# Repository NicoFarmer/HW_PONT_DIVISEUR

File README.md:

# HW_PONT_DIVISEUR
Pont diviseur de tension sur petite carte

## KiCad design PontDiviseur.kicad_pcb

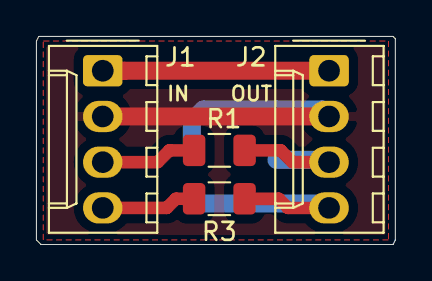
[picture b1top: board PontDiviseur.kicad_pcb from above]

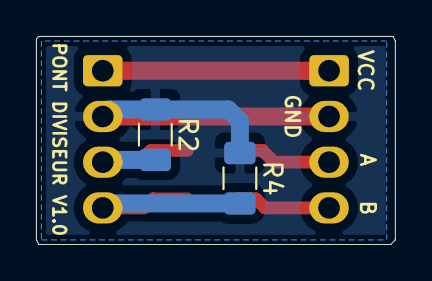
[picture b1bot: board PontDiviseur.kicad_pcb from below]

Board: 2 copper layers, 19.9 x 11.6 mm, 6 parts (2 on the bottom side), 6 nets.

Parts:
J1, J2: Conn_01x04; Molex_KK-254_AE-6410-04A_1x04_P2.54mm_Vertical
R1, R2, R3, R4: R; R_1206_3216Metric

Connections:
/IN_A: J1.3, R1.2
/IN_B: J1.4, R3.2
/OUT_A: J2.3, R1.1, R2.2
/OUT_B: J2.4, R3.1, R4.2
/VCC: J1.1, J2.1
GND: J1.2, J2.2, R2.1, R4.1

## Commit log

2022-10-11 Ajout du sous-module KICAD_LIB
2022-10-11 Version initiale du projet
2022-10-11 Ajout du schéma .pdf
